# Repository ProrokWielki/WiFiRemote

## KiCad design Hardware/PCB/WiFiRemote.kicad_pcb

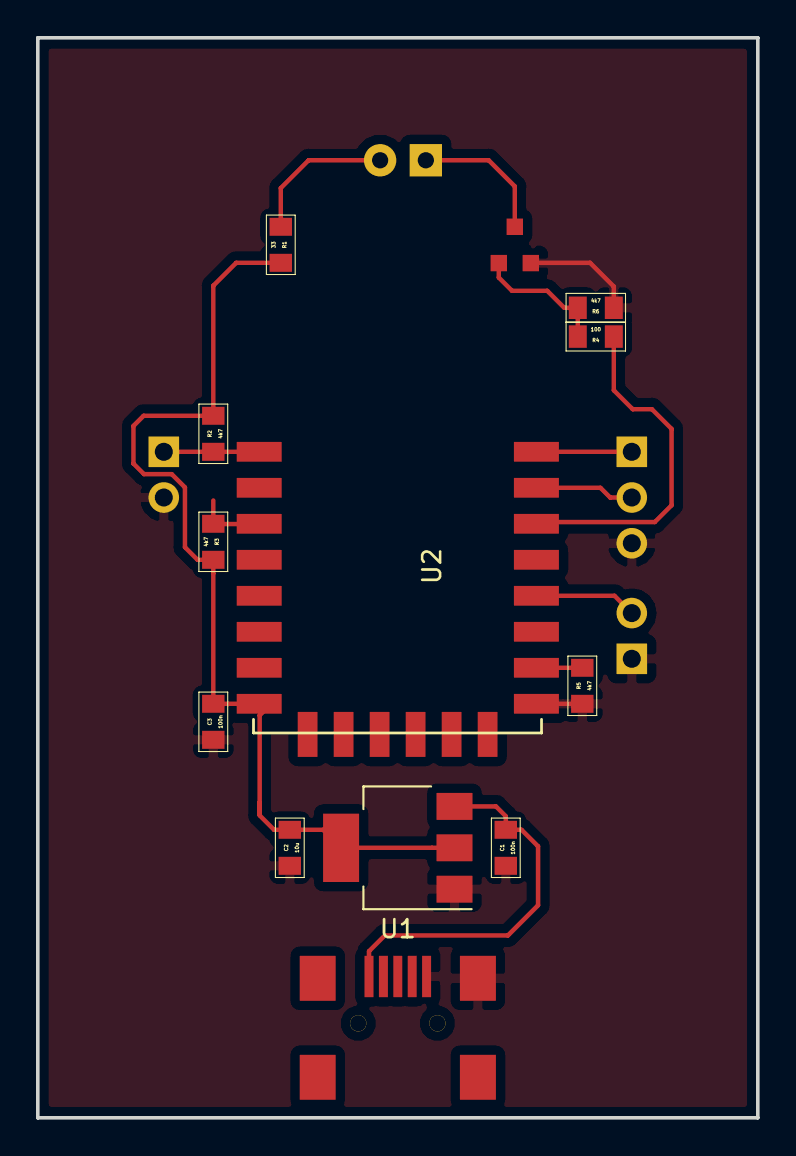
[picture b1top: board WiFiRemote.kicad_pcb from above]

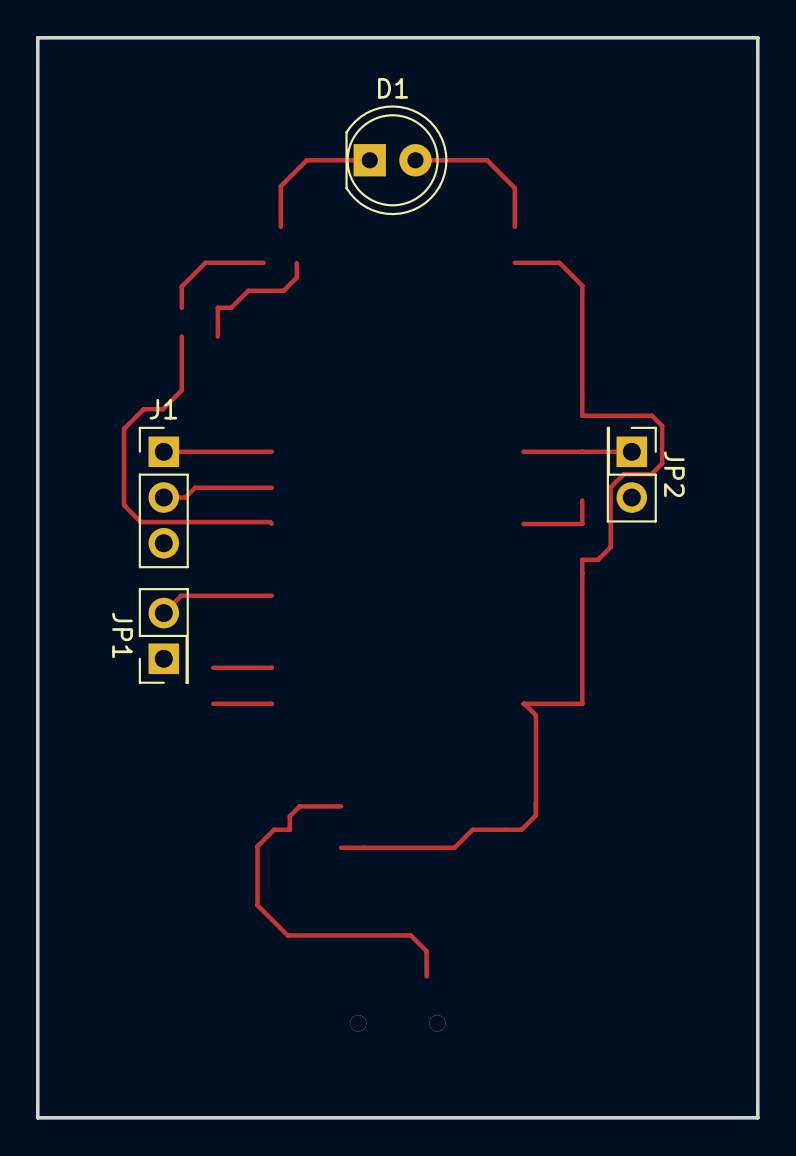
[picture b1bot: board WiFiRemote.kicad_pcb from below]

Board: 2 copper layers, 40.0 x 60.0 mm, 17 parts (4 on the bottom side), 13 nets.

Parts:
C1, C3: 100n; 0805
C2: 10u; 0805
D1: LED; LED_D5.0mm
J1: Tx Rx GND; Pin_Header_Straight_1x03_Pitch2.54mm
J2: USB_B_Mini; USB-MINI-B-SMD
JP1: Program; PinHeader_2x01_P2.54mm_Vertical
JP2: RESET; PinHeader_2x01_P2.54mm_Vertical
Q1: NX7002BK; SOT23-3
R1: 33; 0805
R2, R3, R5, R6: 4k7; 0805
R4: 100; 0805
U1: LD1117-3.3; SOT-223-3_TabPin2
U2: ESP-12E; ESP-12E_SMD

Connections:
+3V3: C2.1, C3.1, R1.1, R2.1, R3.1, U1.2, U2.8
+5V: C1.1, J2.1, U1.3
GNDD: C1.2, C2.2, C3.2, J1.3, J2.5, J2.6, JP1.1, JP2.2, Q1.2, R5.2, R6.2, U1.1, U2.9
unnamed: D1.1, Q1.3
unnamed: D1.2, R1.2
unnamed: J1.1, U2.16
unnamed: J1.2, U2.15
unnamed: JP1.2, U2.12
unnamed: JP2.1, R2.2, U2.1
unnamed: Q1.1, R4.1, R6.1
unnamed: R3.2, U2.3
unnamed: R4.2, U2.14
unnamed: R5.1, U2.10

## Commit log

2020-11-05 added schematic, pcb layout and gerbers
2022-08-16 draft implementation
2022-08-22 added support for airwell rc08b remote
2022-08-22 changed location of airwell_rc08b.h, added documention for rc08b
2022-08-22 added readme and clang-format
2022-08-22 moved README to repo root
2023-05-01 New version of esp_mqtt_helpers.
2023-05-01 Forced station mode.
